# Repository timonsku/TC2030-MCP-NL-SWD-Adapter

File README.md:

# TC2030-MCP-NL-SWD-Adapter

Works for both NL and hook version of course. NL is just what I personally use.
Breaks out the RJ12 connector from the TC2030-MCP to common SWD connectors and standard pin headers.
Tested with actual target PCB to be following the pinout correctly.

BOM
----

- Molex 95501-6669 (RJ12)
- Samtec FTR-105-02-G-D (2x5 pin 1.27mm SMT un-shrouded) (or use the typical shrouded connector) Cheaper here: https://s.click.aliexpress.com/e/_A3X57A
- Molex 90130-1110 (2x5 2.54mm PTH Shrouded)
- Molex 90130-1120 (2x10 2.54mm PTH Shrouded)

For the cable itself, the following Mouser PNs are the MCP variant:

NL version:
- 579-TC2030-MCP-NL 

With hooks:
- 733-53025-851
- 579-TC2030-MCP

For DigiKey:
- TC2030-MCP-NLTC-ND
- TC2030-MCPTC-ND

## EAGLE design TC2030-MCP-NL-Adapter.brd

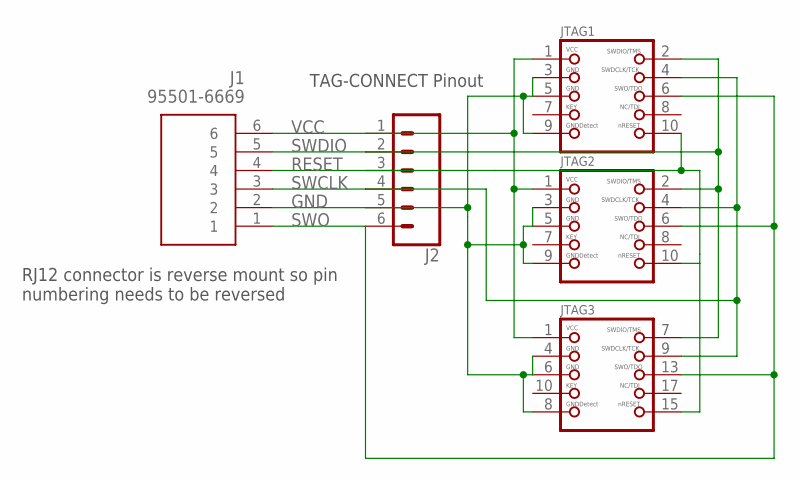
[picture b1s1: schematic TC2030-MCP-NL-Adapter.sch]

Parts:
J1: 95501-6669
J2: CONN_06SILK_FEMALE_PTH; 1X06
JTAG1: JTAG-CORTEXM3; 2X05_1.27MM_SMT
JTAG2: JTAG-CORTEXM3MOLEX; CORTEXM3_SWD10_MOLEX
JTAG3: JTAG-CORTEXM3MOLEX20; JTAG-ARM

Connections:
GND: J1.2, J2.5, JTAG1.3, JTAG1.5, JTAG1.9, JTAG2.3, JTAG2.5, JTAG2.9, JTAG3.4 (3), JTAG3.6 (5), JTAG3.8 (9)
RESET: J1.4, J2.3, JTAG1.10, JTAG2.10, JTAG3.15 (10)
SWCLK: J1.3, J2.4, JTAG1.4, JTAG2.4, JTAG3.9 (4)
SWDIO: J1.5, J2.2, JTAG1.2, JTAG2.2, JTAG3.7 (2)
SWO: J1.1, J2.6, JTAG1.6, JTAG2.6, JTAG3.13 (6)
VCC: J1.6, J2.1, JTAG1.1, JTAG2.1, JTAG3.1

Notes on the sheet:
TAG-CONNECT Pinout
RJ12 connector is reverse mount so pin numbering needs to be reversed

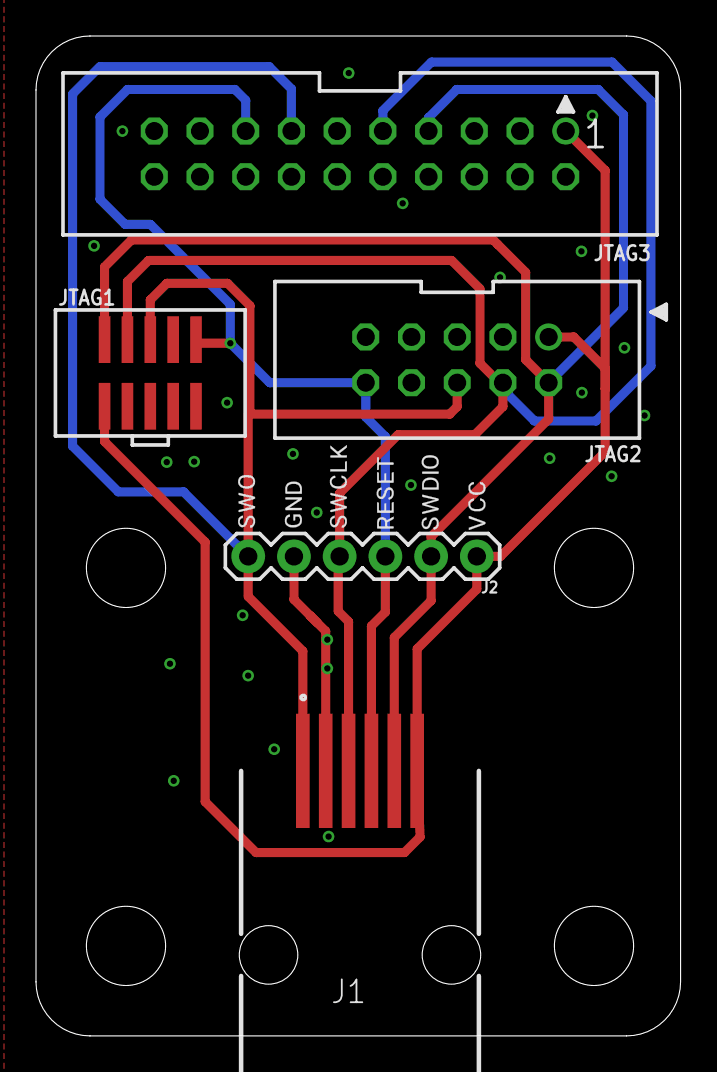
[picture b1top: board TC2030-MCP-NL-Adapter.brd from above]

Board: 2 copper layers, 35.8 x 55.5 mm, 11 parts (0 on the bottom side), 6 nets.

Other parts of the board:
U$1: SWO0
U$2: GND0
U$3: SWCLK0
U$4: RESET0
U$5: SWDIO0
U$6: VCC0

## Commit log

2021-07-11 add board files
2021-07-11 add BOM
2021-07-11 rename gerbers archive
2021-07-11 readme changes
2021-12-26 add pn for cable
2023-02-13 fix SWDIO short to GND

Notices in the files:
parts and their libraries:
SparkFun-Connectors: Licensing: Creative Commons ShareAlike 4.0 International - https://creativecommons.org/licenses/by-sa/4.0
microbuilder: This work is placed in the public domain, and may be freely used for commercial and non-commercial work with the following conditions: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
